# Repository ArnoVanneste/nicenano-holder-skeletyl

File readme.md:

## Holder PCB for the Elite-C

Universal holder PCB for all Bastard Keyboards

## Optional features

- handedness resistor: 5.1k on R6, use pin F1
- I2C: install 4.7k resistors on R2 and R4
- on/off switch: use MSK-12C01-07

## Forks

[Holiot carrier](https://github.com/vattern/holiot-carrier) for bluetooth

[Splinktegrated](https://github.com/bastardkb/splinktegrated) - Integrated rp2040 and usb-c daughterboard 

[Blackpill holder](https://github.com/Bastardkb/adapter-blackpill/)

[Nice!nano holder](https://github.com/victorlucachi/Elite-C-holder)

# License 

This work is licensed under a Creative Commons Attribution-NonCommercial-ShareAlike 4.0 International License.

## Components

- JST connector: [Hirose Electric Co Ltd DF3-2P-2DSA(01)](https://www.digikey.be/en/products/detail/hirose-electric-co-ltd/DF3-2P-2DSA-01/413121)
- Flat ribbon cable, flex strip format with 2.54mm pitch. I want to paint them black with vinyl dye.
- Reset button: [5x5x6 rubber smd button]()

## To Do
[ ] Find flex stip ribbon cable and where to buy the black jst connector.
[ ] Edit the 3D print to remove the headphone jack hole.
[ ] Edit the thumb and key flex pcb's to remove LED light spot.
[x] Edit holder pcb to accomodate new reset button and remove all unused sections.

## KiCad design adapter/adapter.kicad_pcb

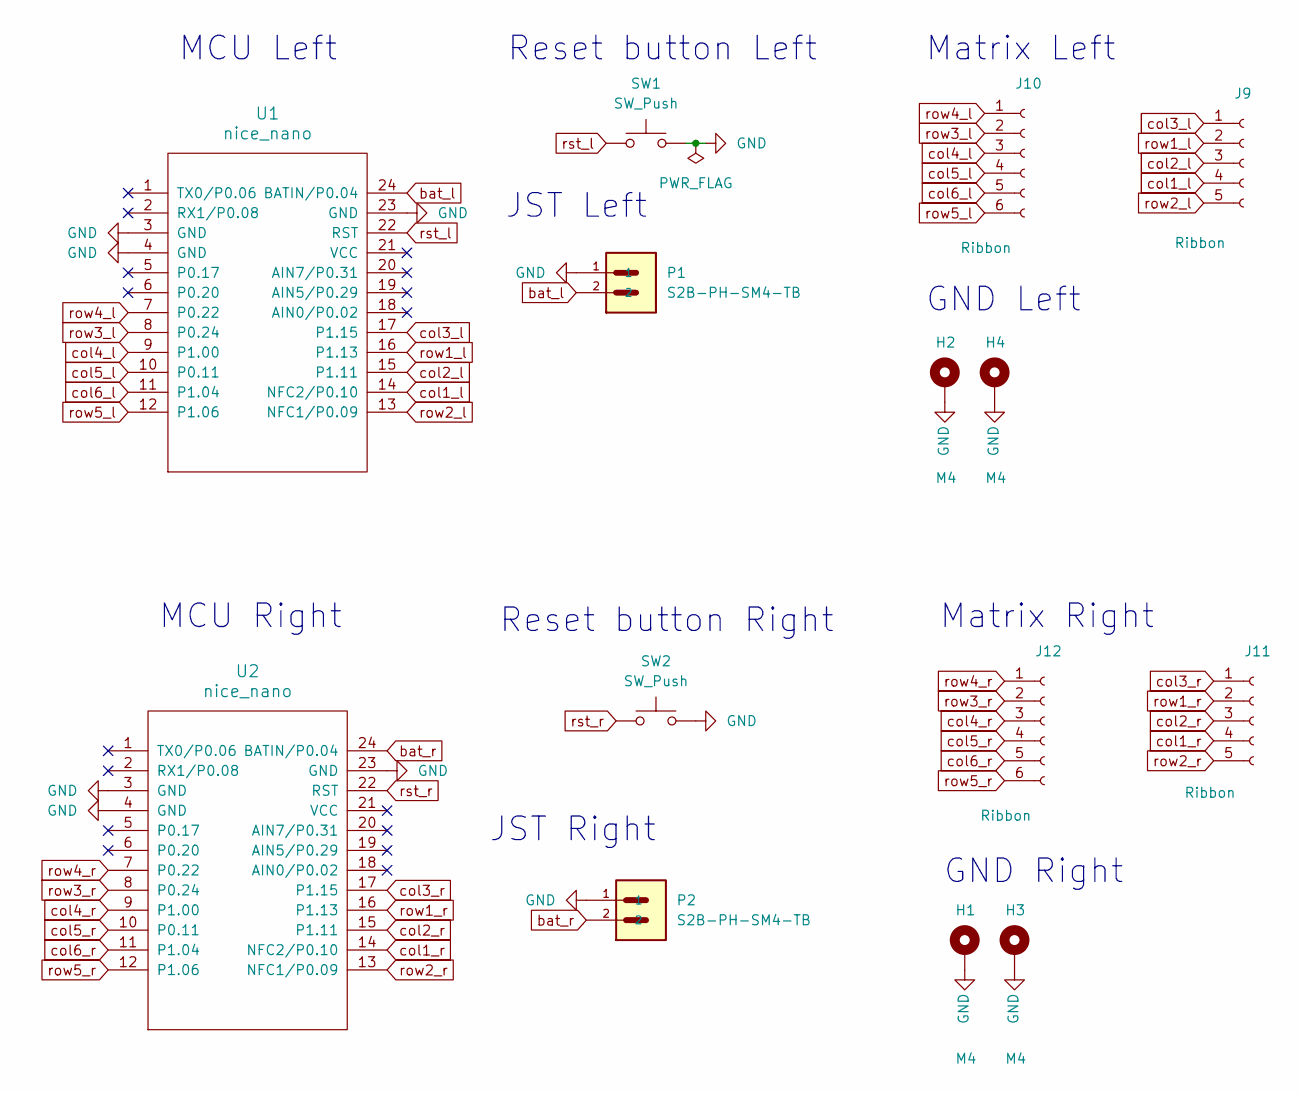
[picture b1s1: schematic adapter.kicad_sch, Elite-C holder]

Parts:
H1, H2, H3, H4: M4; MountingHole_4mm_Pad_thin
J9, J11: Ribbon; 5_PinHeader
J10, J12: Ribbon; 6_PinHeader
P1, P2: S2B-PH-SM4-TB; JST_S2B-PH-SM4-TB
SW1, SW2: SW_Push; SW_Tactile_3x3_SMD_H1p5
U1, U2: nice_nano

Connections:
GND: H1.1, H2.1, H3.1, H4.1, P1.1, P2.1, SW1.2, SW2.2, U1.3 (GND), U1.4 (GND), U1.23 (GND), U2.3 (GND), U2.4 (GND), U2.23 (GND)
bat_l: P1.2, U1.24 (BATIN/P0.04)
bat_r: P2.2, U2.24 (BATIN/P0.04)
col1_l: J9.4, U1.14 (NFC2/P0.10)
col1_r: J11.4, U2.14 (NFC2/P0.10)
col2_l: J9.3, U1.15 (P1.11)
col2_r: J11.3, U2.15 (P1.11)
col3_l: J9.1, U1.17 (P1.15)
col3_r: J11.1, U2.17 (P1.15)
col4_l: J10.3, U1.9 (P1.00)
col4_r: J12.3, U2.9 (P1.00)
col5_l: J10.4, U1.10 (P0.11)
col5_r: J12.4, U2.10 (P0.11)
col6_l: J10.5, U1.11 (P1.04)
col6_r: J12.5, U2.11 (P1.04)
row1_l: J9.2, U1.16 (P1.13)
row1_r: J11.2, U2.16 (P1.13)
row2_l: J9.5, U1.13 (NFC1/P0.09)
row2_r: J11.5, U2.13 (NFC1/P0.09)
row3_l: J10.2, U1.8 (P0.24)
row3_r: J12.2, U2.8 (P0.24)
row4_l: J10.1, U1.7 (P0.22)
row4_r: J12.1, U2.7 (P0.22)
row5_l: J10.6, U1.12 (P1.06)
row5_r: J12.6, U2.12 (P1.06)
rst_l: SW1.1, U1.22 (RST)
rst_r: SW2.1, U2.22 (RST)

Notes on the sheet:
GND Left
Reset button Left
GND Right
JST Left
Matrix Left
JST Right
Reset button Right
MCU Left
MCU Right
Matrix Right

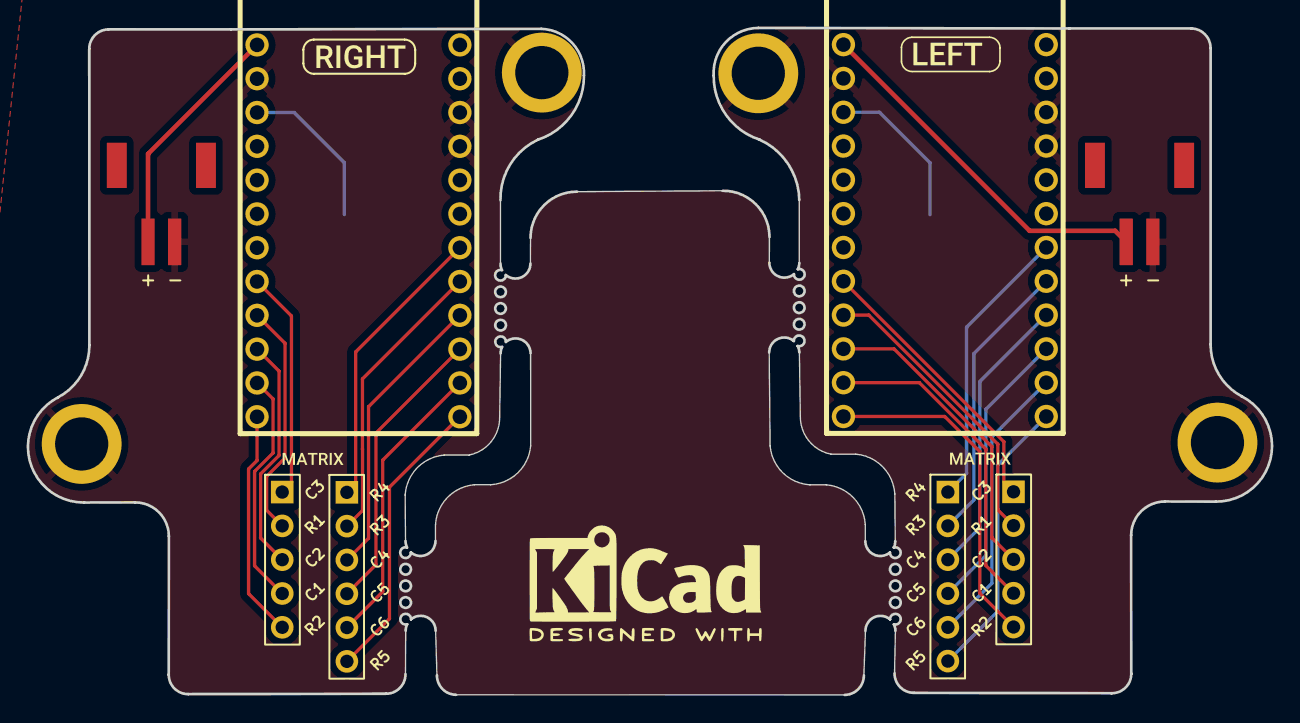
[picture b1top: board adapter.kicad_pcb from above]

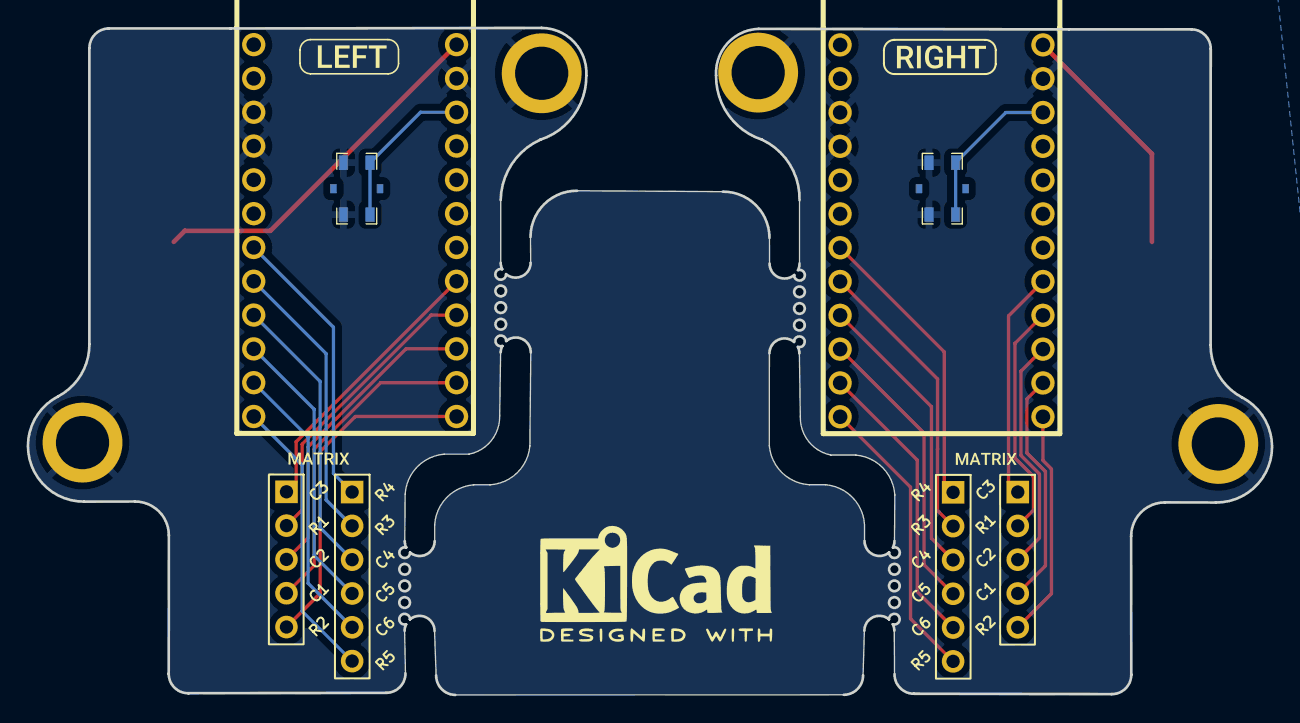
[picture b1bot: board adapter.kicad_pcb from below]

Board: 2 copper layers, 93.5 x 50.1 mm, 22 parts (8 on the bottom side), 27 nets.

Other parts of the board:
kibuzzard-61F01B61, kibuzzard-61F01B61#2: G***; kibuzzard-61F01B61
kibuzzard-61F01940, kibuzzard-61F01940#2, kibuzzard-61F01940#3, kibuzzard-61F01940#4: G***; kibuzzard-61F01940
kibuzzard-6208EFFE, kibuzzard-6208EFFE#2: G***; kibuzzard-6208EFFE

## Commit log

2026-01-21 Remove all of the components except matrix pins and add nice!nano schematic from github
2026-01-21 Add nice!nano mcu to right side
2026-01-22 Cleanup all the leftover silkscreen from removed parts
2026-01-22 Add jst connector and powerswitch
2026-01-22 Add a resetbutton
2026-01-22 Add components to readme
2026-01-26 Update readme with new all black plan!
2026-01-26 Remove power switch
2026-01-26 Add new power switch and reset button
2026-01-26 Place all the components onto the pcb
2026-01-26 Remove 3 unused nice nano pins
2026-01-26 Connect all the components in the schematic
2026-01-26 Fix all the pcb routes
2026-01-27 Fix routes in pcb view
2026-01-27 Solve all ERC errors
2026-01-27 Update silk off power switch
2026-01-27 Cleanup the silk
2026-01-28 Removed the powerswitch, reset button and jst connector + fixed the corner extention
2026-01-28 Add custom reset switch
2026-01-29 Add JST connectors and cleaned up the PCB

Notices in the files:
adapter/adapter.kicad_sch:
Licensed under CERN-OHL-W v2
